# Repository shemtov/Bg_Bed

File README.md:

# BG Bed firmware

This repository contains the firmware source for six installed modules and several auxiliary experiments. Open each module's directory as its own PlatformIO project. The table below is a **source inventory**, not permission to flash every module.

| Module | Directory | Source baseline | Status on 2026-10-04 |
|---|---|---:|---|
| Audio Node | `audionode/` | TEST055 | Candidate paired with Listener TEST030; clear Dream playback reported, but waits for full-file transfer. |
| Listener | `listener/` | TEST030 | Candidate paired with Audio Node TEST055; microphones and SD stay installed here. |
| Shemi panel | `panel_shemi/` | TEST105 | Wait animation candidate; flashing and build status must be confirmed on the actual panel. |
| Ira panel | `panel_ira/` | TEST119 | Wait animation candidate; flashing and build status must be confirmed on the actual panel. |
| Shemi BedBox | `bedbox_shemi/` | TEST024 in earlier cloud tree | Its source says **not yet run on hardware**; identify the firmware actually installed before replacing it. |
| Ira BedBox | `bedbox_ira/` | TEST001 in earlier cloud tree | **Motor diagnostic, runs on boot. Do not flash as production firmware.** Obtain the deployed firmware. |

The first four projects were reconciled from the latest small update packages prepared for the BG Bed system. Their `TEST_NUMBER` values were corrected to match their source headers and terminal banners. Neither a local PlatformIO build nor a six-board hardware regression was available in the preparation workspace. Do not treat repository presence as hardware validation.

The panel code depends on the board description and graphics/Waveshare libraries in `panel_shemi/`. `panel_ira/platformio.ini` uses that library directory on PlatformIO Core 6.x instead of duplicating a large vendor tree. Keep `panel_shemi/lib/` until builds of both panels pass in a clean checkout. The upstream platform in the project files currently tracks a `stable` release URL; pin a tested platform release after reproducing all builds.

## Release discipline

1. Record the **installed test number** and backup from each module before any flash. The source inventory above may differ from what is installed.
2. Build and flash matching protocol pairs, especially Audio Node TEST055 and Listener TEST030. Verify both panels, then exercise radio, Dream record/play, RS485, alarm and each side's massage independently.
3. Keep Ira BedBox out of every bulk-flash target until its actual production firmware is recovered and tested. The same caution applies to Shemi BedBox TEST024.
4. Next work: implement buffered Dream streaming without moving microphones/SD, then Edge Impulse voice recognition on the Listener. These features are **planned**, not present in this baseline.

The parent of the repository's September 7 `main` commit was `f267bd438197469405629a1d09cf4d9c6c69ba74`, the historical “KNOWN GOOD” marker for earlier Shemi/Ira panels. Preserve it as a rollback reference. Repository cleanup removes logs/WAV and credential-like files from the current tracked tree, but old Git commits still contain them. Rotate any active credentials and decide separately whether a coordinated history cleanup is required.

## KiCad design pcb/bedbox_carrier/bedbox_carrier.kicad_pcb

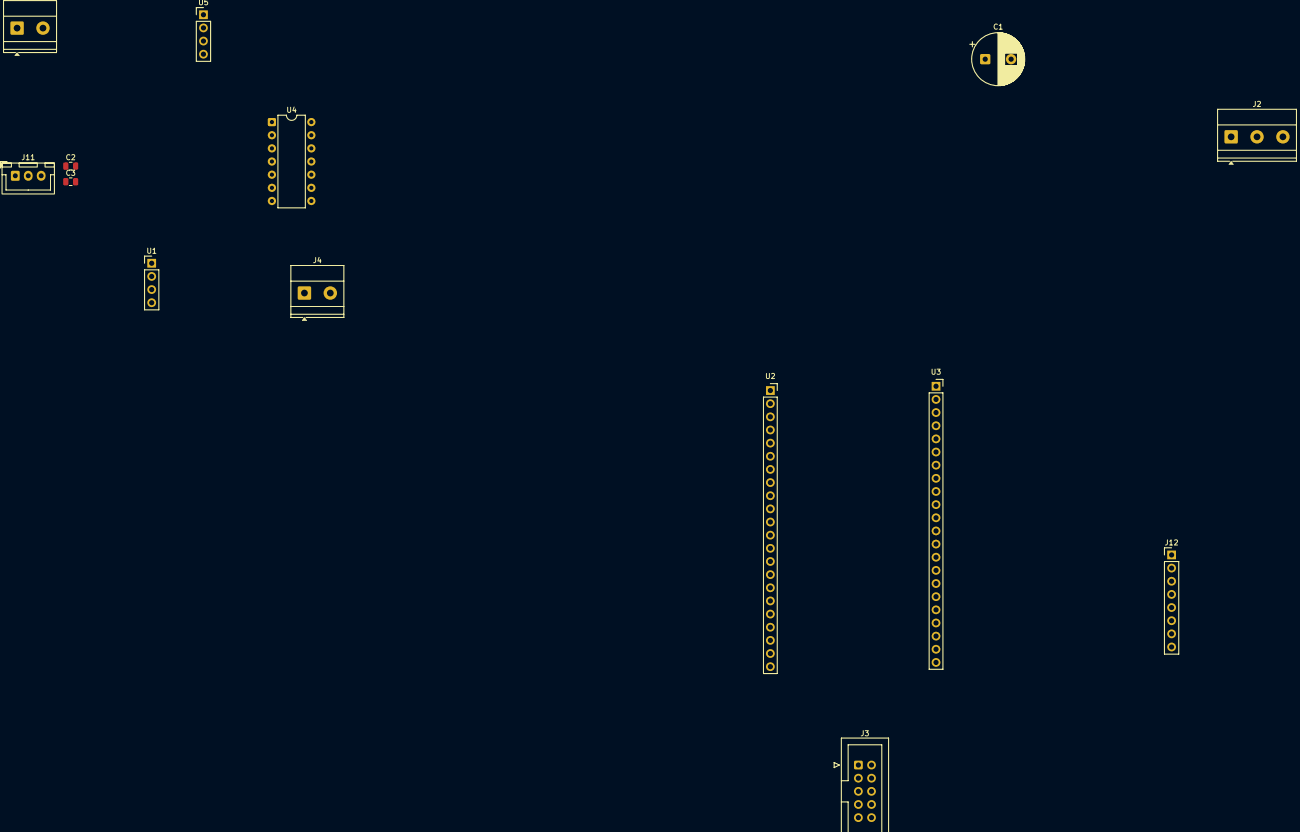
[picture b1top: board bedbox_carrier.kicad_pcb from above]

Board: 2 copper layers, 14 parts (0 on the bottom side), 22 nets, no tracks yet.

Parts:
C1: 1000uF 25V; CP_Radial_D10.0mm_P5.00mm
C2, C3: 100nF; C_0805_2012Metric
J1: 12V IN; TerminalBlock_Phoenix_MKDS-1,5-2_1x02_P5.00mm_Horizontal
J2: RS485 A B GND; TerminalBlock_Phoenix_MKDS-1,5-3_1x03_P5.00mm_Horizontal
J3: PWM 1-8 IDC; IDC-Header_2x05_P2.54mm_Vertical
J4: 12V OUT to L298N; TerminalBlock_Phoenix_MKDS-1,5-2_1x02_P5.00mm_Horizontal
J11: WS2815 strip; JST_XH_B3B-XH-A_1x03_P2.50mm_Vertical
J12: SPARE GPIO; PinHeader_1x08_P2.54mm_Vertical
U1: BUCK 12V-5V 3A; PinHeader_1x04_P2.54mm_Vertical
U2: ESP32-S3 LEFT; PinSocket_1x22_P2.54mm_Vertical
U3: ESP32-S3 RIGHT; PinSocket_1x22_P2.54mm_Vertical
U4: 74AHCT125; DIP-14_W7.62mm
U5: RS485 auto module; PinHeader_1x04_P2.54mm_Vertical

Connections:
+5V: C2.1, C3.1, U1.3, U2.1, U4.14, U5.1
+12V: C1.1, J4.1, J11.1, U1.1
GND: C1.2, C2.2, C3.2, J1.2, J2.3, J3.9, J3.10, J4.2, J11.3, J12.8, U1.2, U1.4, U2.2, U3.1, U4.7, U5.2
LED_DATA_3V3: U3.12, U4.2
LED_DATA_5V: J11.2, U4.3
PWM1: J3.1, U2.5
PWM2: J3.2, U2.6
PWM3: J3.3, U2.7
PWM4: J3.4, U2.8
PWM5: J3.5, U3.5
PWM6: J3.6, U3.6
PWM7: J3.7, U3.7
PWM8: J3.8, U3.8
RS485_RX: U2.11, U5.4
RS485_TX: U2.10, U5.3
SPARE1: J12.1, U3.15
SPARE2: J12.2, U3.16
SPARE3: J12.3, U3.17
SPARE4: J12.4, U3.18
SPARE5: J12.5, U3.19
SPARE6: J12.6, U3.20
SPARE_3V3: J12.7, U3.2
